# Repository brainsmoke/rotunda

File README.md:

Rotunda
========

Charlieplexed PCB polyhedron

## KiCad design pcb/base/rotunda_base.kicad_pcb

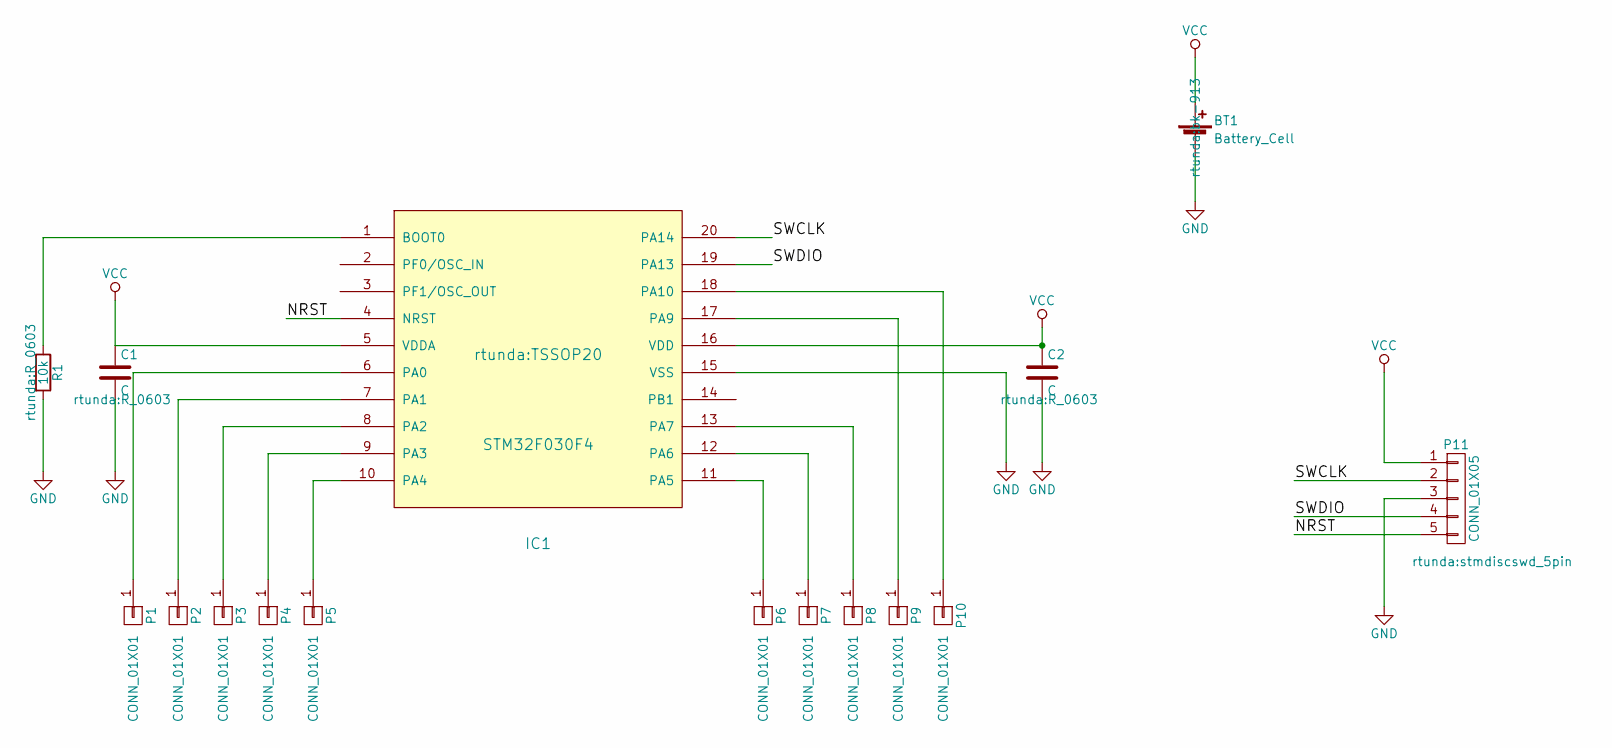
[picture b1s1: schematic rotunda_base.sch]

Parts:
BT1: Battery_Cell; bk-913
C1, C2: C; R_0603
IC1: STM32F030F4; TSSOP20
P1, P2, P3, P4, P5, P6, P7, P8, P9, P10: CONN_01X01; pin
P11: CONN_01X05; stmdiscswd_5pin
R1: 10k; R_0603

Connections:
/NRST: IC1.4 (NRST), P11.5
/SWCLK: IC1.20 (PA14), P11.2
/SWDIO: IC1.19 (PA13), P11.4
GND: BT1.2 (-), C1.2, C2.2, IC1.15 (VSS), P11.3, R1.2
unnamed: IC1.1 (BOOT0), R1.1
unnamed: IC1.6 (PA0), P1.1
unnamed: IC1.7 (PA1), P2.1
unnamed: IC1.8 (PA2), P3.1
unnamed: IC1.9 (PA3), P4.1
unnamed: IC1.10 (PA4), P5.1
unnamed: IC1.11 (PA5), P6.1
unnamed: IC1.12 (PA6), P7.1
unnamed: IC1.13 (PA7), P8.1
unnamed: IC1.17 (PA9), P9.1
unnamed: IC1.18 (PA10), P10.1
VCC: BT1.1 (+), C1.1, C2.1, IC1.5 (VDDA), IC1.16 (VDD), P11.1

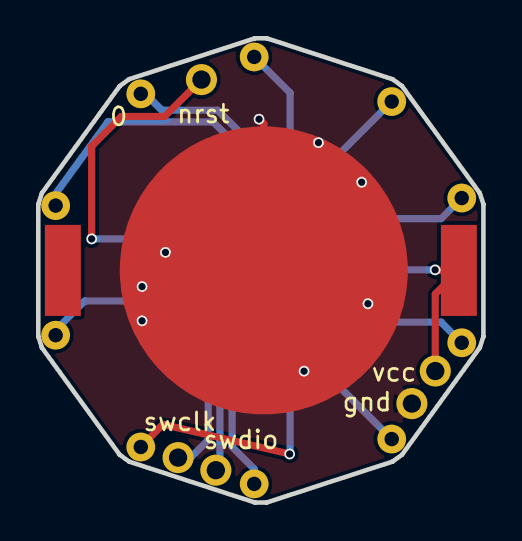
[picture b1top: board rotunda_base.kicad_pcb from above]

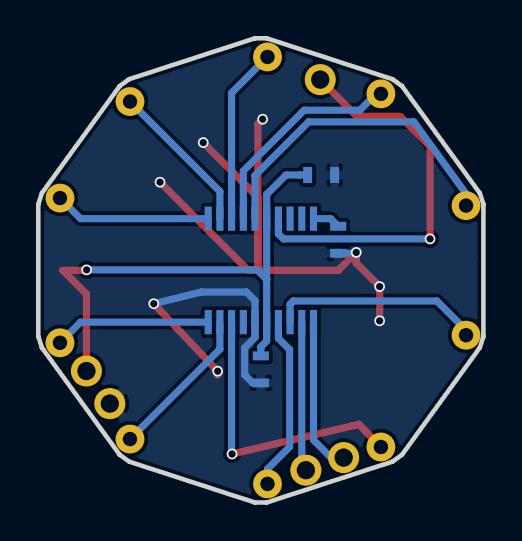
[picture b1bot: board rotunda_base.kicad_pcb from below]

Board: 2 copper layers, 24.7 x 25.8 mm, 16 parts (15 on the bottom side), 16 nets.

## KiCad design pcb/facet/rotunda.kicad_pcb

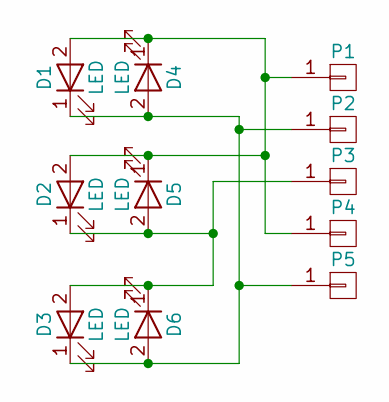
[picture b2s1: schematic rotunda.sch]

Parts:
D1, D2, D3, D4, D5, D6: LED; LED_0603
P1, P2, P3, P4, P5: CONN_01X01; pin

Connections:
unnamed: D1.1 (K), D3.1 (K), D4.2 (A), D6.2 (A), P2.1, P5.1
unnamed: D1.2 (A), D2.2 (A), D4.1 (K), D5.1 (K), P1.1, P4.1
unnamed: D2.1 (K), D3.2 (A), D5.2 (A), D6.1 (K), P3.1

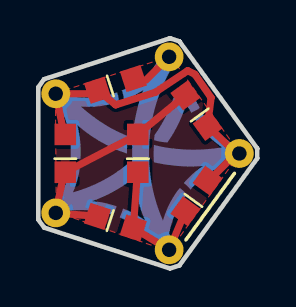
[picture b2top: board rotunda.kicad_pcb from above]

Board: 2 copper layers, 12.2 x 12.8 mm, 11 parts (0 on the bottom side), 3 nets.

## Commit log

2017-08-28 rotunda charlieplexed PCB polyhedron
